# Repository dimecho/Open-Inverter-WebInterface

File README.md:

# Open Inverter - Alternative Web Interface

Alternative Web Interface for [OpenInverter.org Project](https://openinverter.org/forum)

- Inverter [Hardware](https://github.com/jsphuebner/inverter-hardware)
- Inverter [Firmware](https://github.com/jsphuebner/stm32-sine)
- Original [Web Interface](https://github.com/jsphuebner/esp8266-web-interface)

## Features

> **All-in-One**
> * RS232-USB Drivers
> * Inverter Parameters
> * Sensor Graphs
> * Firmware Flash
> * Wiring Diagrams
> * PCB Schematics
> * Component List
> * Encoder Builder
> * IGBT Test
> * CAN Setup
> * Auto Tunning
> * Source Code Compilers

## Screenshot

## Download

 [Download for Mac](../../releases/download/1.0/Open.Inverter.Web.dmg)

 [Download for Windows](../../releases/download/1.0/Open.Inverter.Web.zip)

 [Download for Linux](../../releases/download/1.0/Open.Inverter.Web.tgz)

 [Download for ESP8266](../../releases/download/1.0/Open.Inverter.ESP8266.zip)

 [Download for RaspberryPi](../../releases/download/1.0/Open.Inverter.Pi.zip)

## Author

Dima Dykhman

## Licenses

> Console Management
>
> 
>
> Inverter Hardware
>
> 
>
> Inverter Software
>
>

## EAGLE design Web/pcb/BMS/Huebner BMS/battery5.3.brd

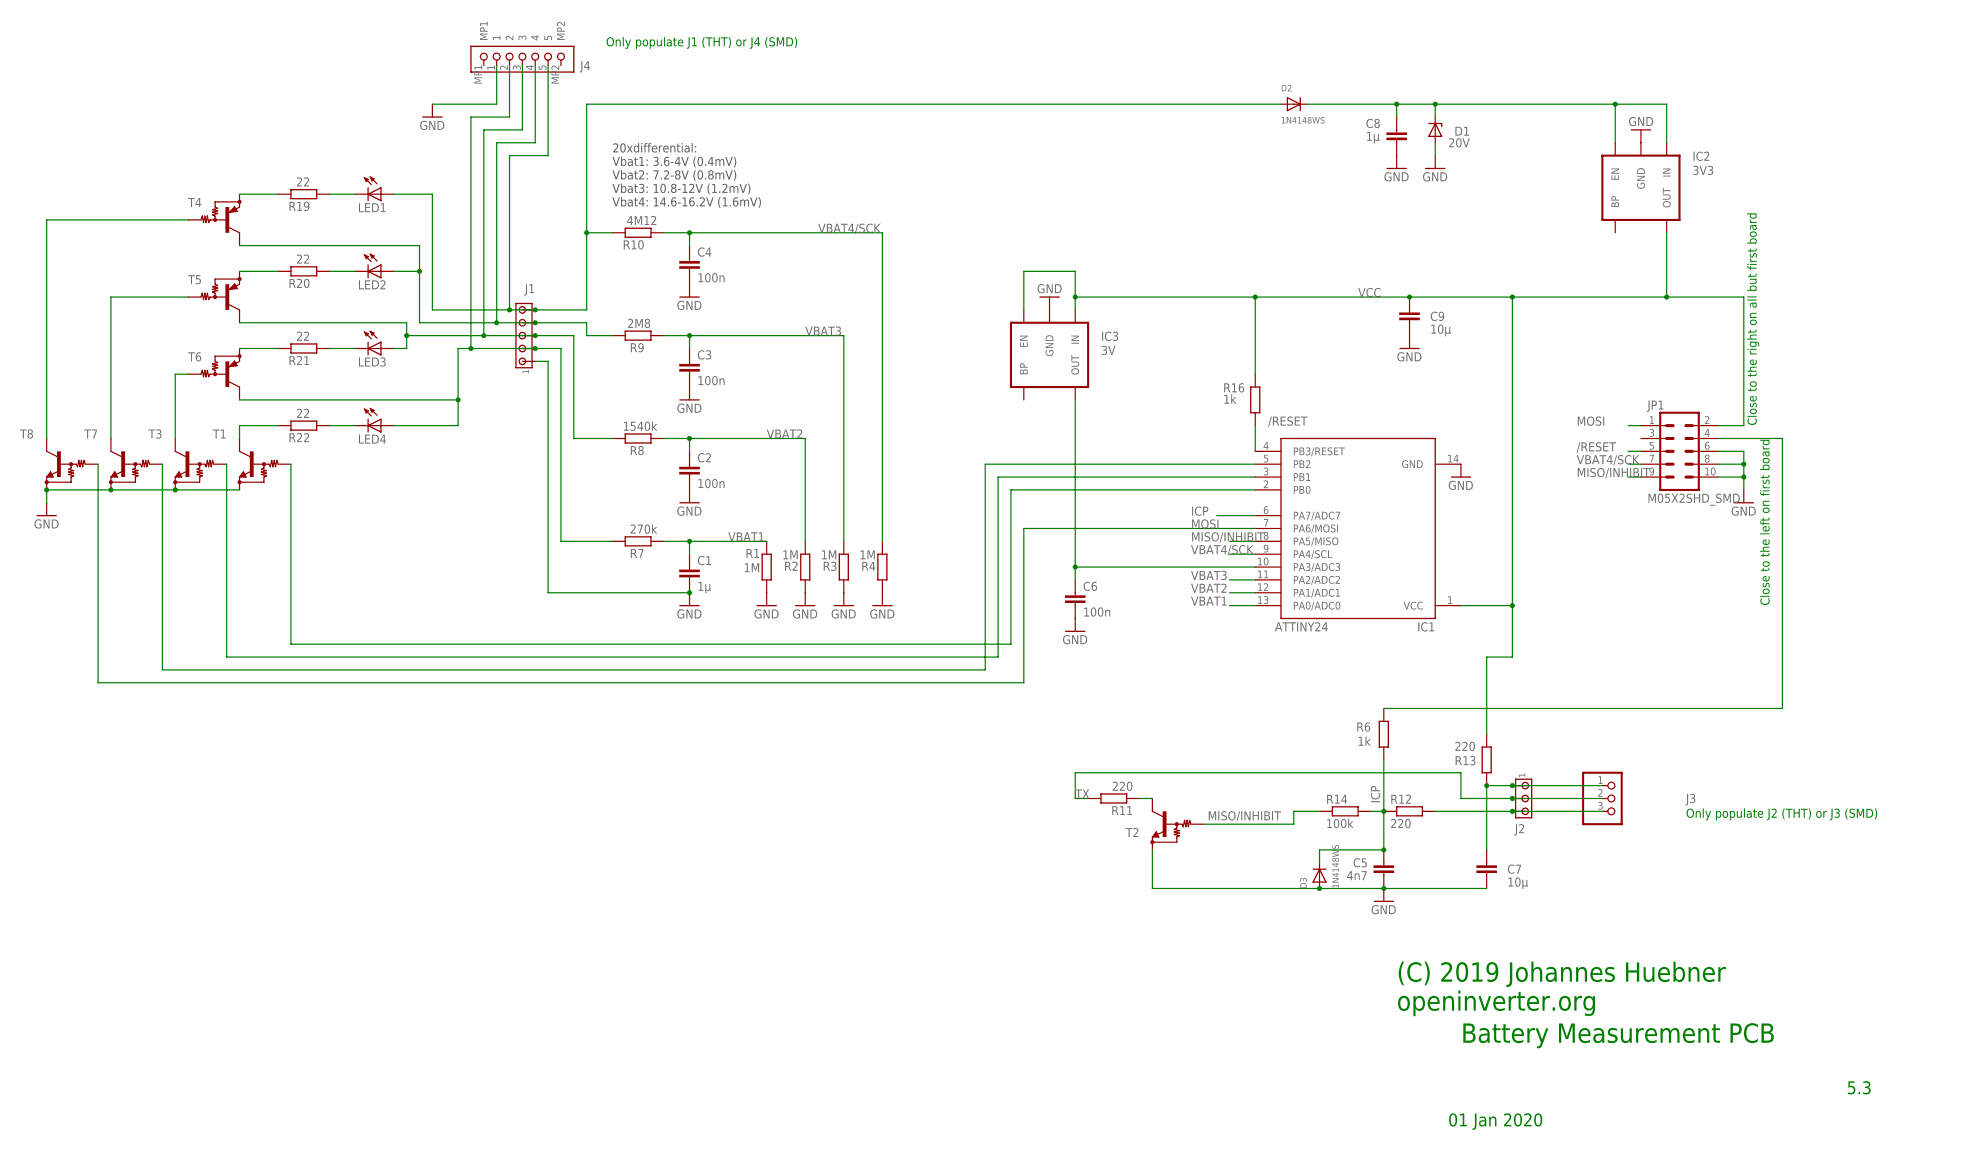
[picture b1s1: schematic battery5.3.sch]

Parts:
C1: 1µ; C0603
C2, C3, C4, C6: 100n; C0603
C5: 4n7; C0603
C7, C9: 10µ; C0805
C8: 1µ; C0805
D1: 20V; SMB
D2, D3: 1N4148WS; SOD-323F
IC1: ATTINY24; SO014
IC2: 3V3; SOT23-5
IC3: 3V; SOT23-5
J1: MTA05-100; 10X05MTA
J2: MTA03-100; 10X03MTA
J3: JST_3PIN; JSTPH3
J4: BM05B-PASS-1-TFT_(LF)(SN)SMD; BM05BPASS1TFTLFSN
JP1: M05X2SHD_SMD; 2X5-SHROUDED_SMD
LED1, LED2, LED3, LED4: 150060GS75000; CHIPLED_0805
R1, R2, R3, R4: 1M; R0603
R6, R16: 1k; R0603
R7: 270k; R0603
R8: 1540k; R0603
R9: 2M8; R0603
R10: 4M12; R0603
R11, R12, R13: 220; R0603
R14: 100k; R0603
R19, R20, R21, R22: 22; R0805
T1, T2, T3, T7, T8: MMUN2233; SC59-BEC
T4, T5, T6: MMUN2111LT1G; SC59-BEC

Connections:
/RESET: IC1.4 (PB3/RESET), JP1.5, R16.2
GND: C1.2, C2.2, C3.2, C4.2, C5.2, C6.2, C7.2, C8.2, C9.2, D1.A, D3.A, IC1.14 (GND), IC2.2 (GND), IC3.2 (GND), J1.1, J4.1, JP1.6, JP1.8, JP1.10, R1.2, R2.2, R3.2, R4.2, T1.E, T2.E, T3.E, T7.E, T8.E
ICP: C5.1, D3.C, IC1.6 (PA7/ADC7), R6.1, R12.1, R14.2
MISO/INHIBIT: IC1.8 (PA5/MISO), JP1.9, R14.1, T2.B
MOSI: IC1.7 (PA6/MOSI), JP1.1, T8.B
unnamed: T3.C, T6.B
unnamed: C6.1, IC1.10 (PA3/ADC3), IC3.5 (OUT)
unnamed: IC1.2 (PB0), T1.B
unnamed: IC1.3 (PB1), T3.B
unnamed: R19.2, T4.E
unnamed: LED1.C, R19.1
unnamed: JP1.4, R6.2
unnamed: IC1.5 (PB2), T7.B
unnamed: R20.2, T5.E
unnamed: C7.1, J2.1, J3.1, R13.2
unnamed: LED2.C, R20.1
unnamed: R11.1, T2.C
unnamed: D2.A, J1.5, J4.5, LED1.A, R10.2
unnamed: LED3.C, R21.1
unnamed: LED4.C, R22.1
unnamed: R21.2, T6.E
unnamed: R22.2, T1.C
unnamed: J2.3, J3.3, R12.2
unnamed: J1.4, J4.4, LED2.A, R9.2, T4.C
unnamed: J1.3, J4.3, LED3.A, R8.2, T5.C
unnamed: J1.2, J4.2, LED4.A, R7.2, T6.C
unnamed: T5.B, T7.C
unnamed: T4.B, T8.C
TX: J2.2, J3.2, R11.2
VBAT: C8.1, D1.C, D2.C, IC2.1 (IN), IC2.3 (EN)
VBAT1: C1.1, IC1.13 (PA0/ADC0), R1.1, R7.1
VBAT2: C2.1, IC1.12 (PA1/ADC1), R2.1, R8.1
VBAT3: C3.1, IC1.11 (PA2/ADC2), R3.1, R9.1
VBAT4/SCK: C4.1, IC1.9 (PA4/SCL), JP1.7, R4.1, R10.1
VCC: C9.1, IC1.1 (VCC), IC2.5 (OUT), IC3.1 (IN), IC3.3 (EN), JP1.2, R13.1, R16.1

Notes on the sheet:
20xdifferential: Vbat1: 3.6-4V (0.4mV) Vbat2: 7.2-8V (0.8mV) Vbat3: 10.8-12V (1.2mV) Vbat4: 14.6-16.2V (1.6mV)
Close to the right on all but first board
5.3
(C) 2019 Johannes Huebner openinverter.org
Battery Measurement PCB
01 Jan 2020
Only populate J2 (THT) or J3 (SMD)
Only populate J1 (THT) or J4 (SMD)
Close to the left on first board

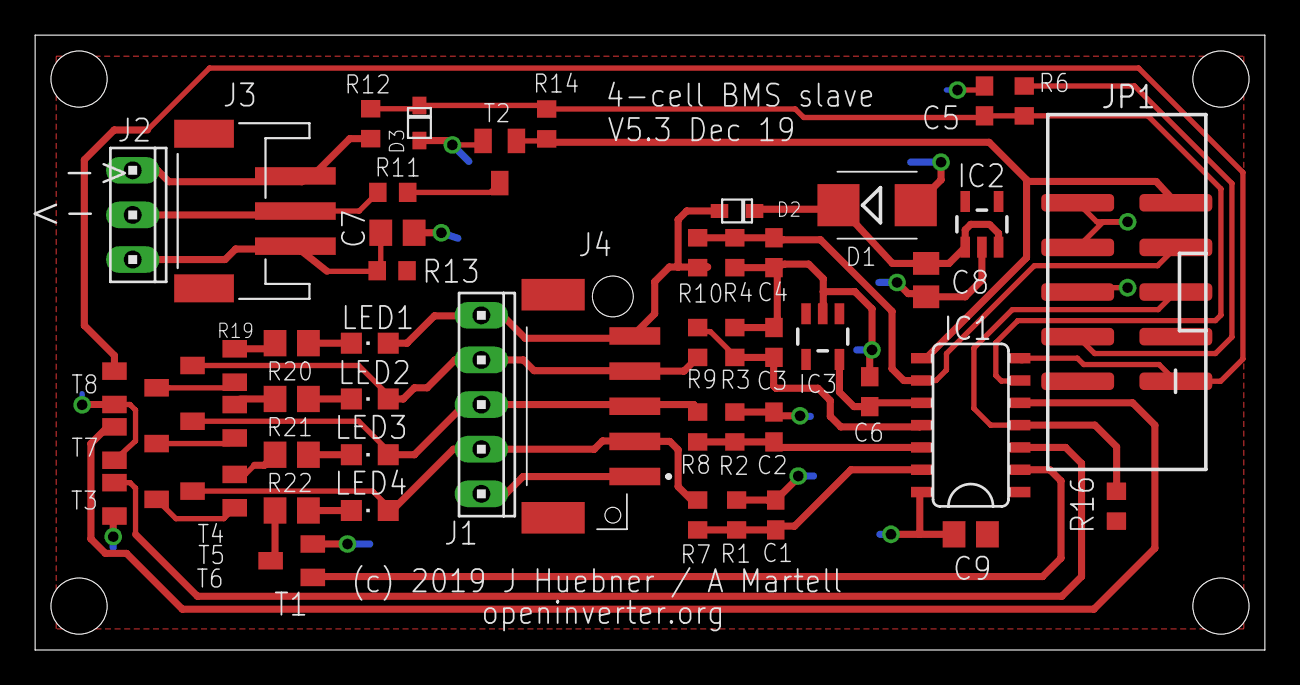
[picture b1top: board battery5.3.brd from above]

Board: 2 copper layers, 70.0 x 35.0 mm, 50 parts (0 on the bottom side), 35 nets.

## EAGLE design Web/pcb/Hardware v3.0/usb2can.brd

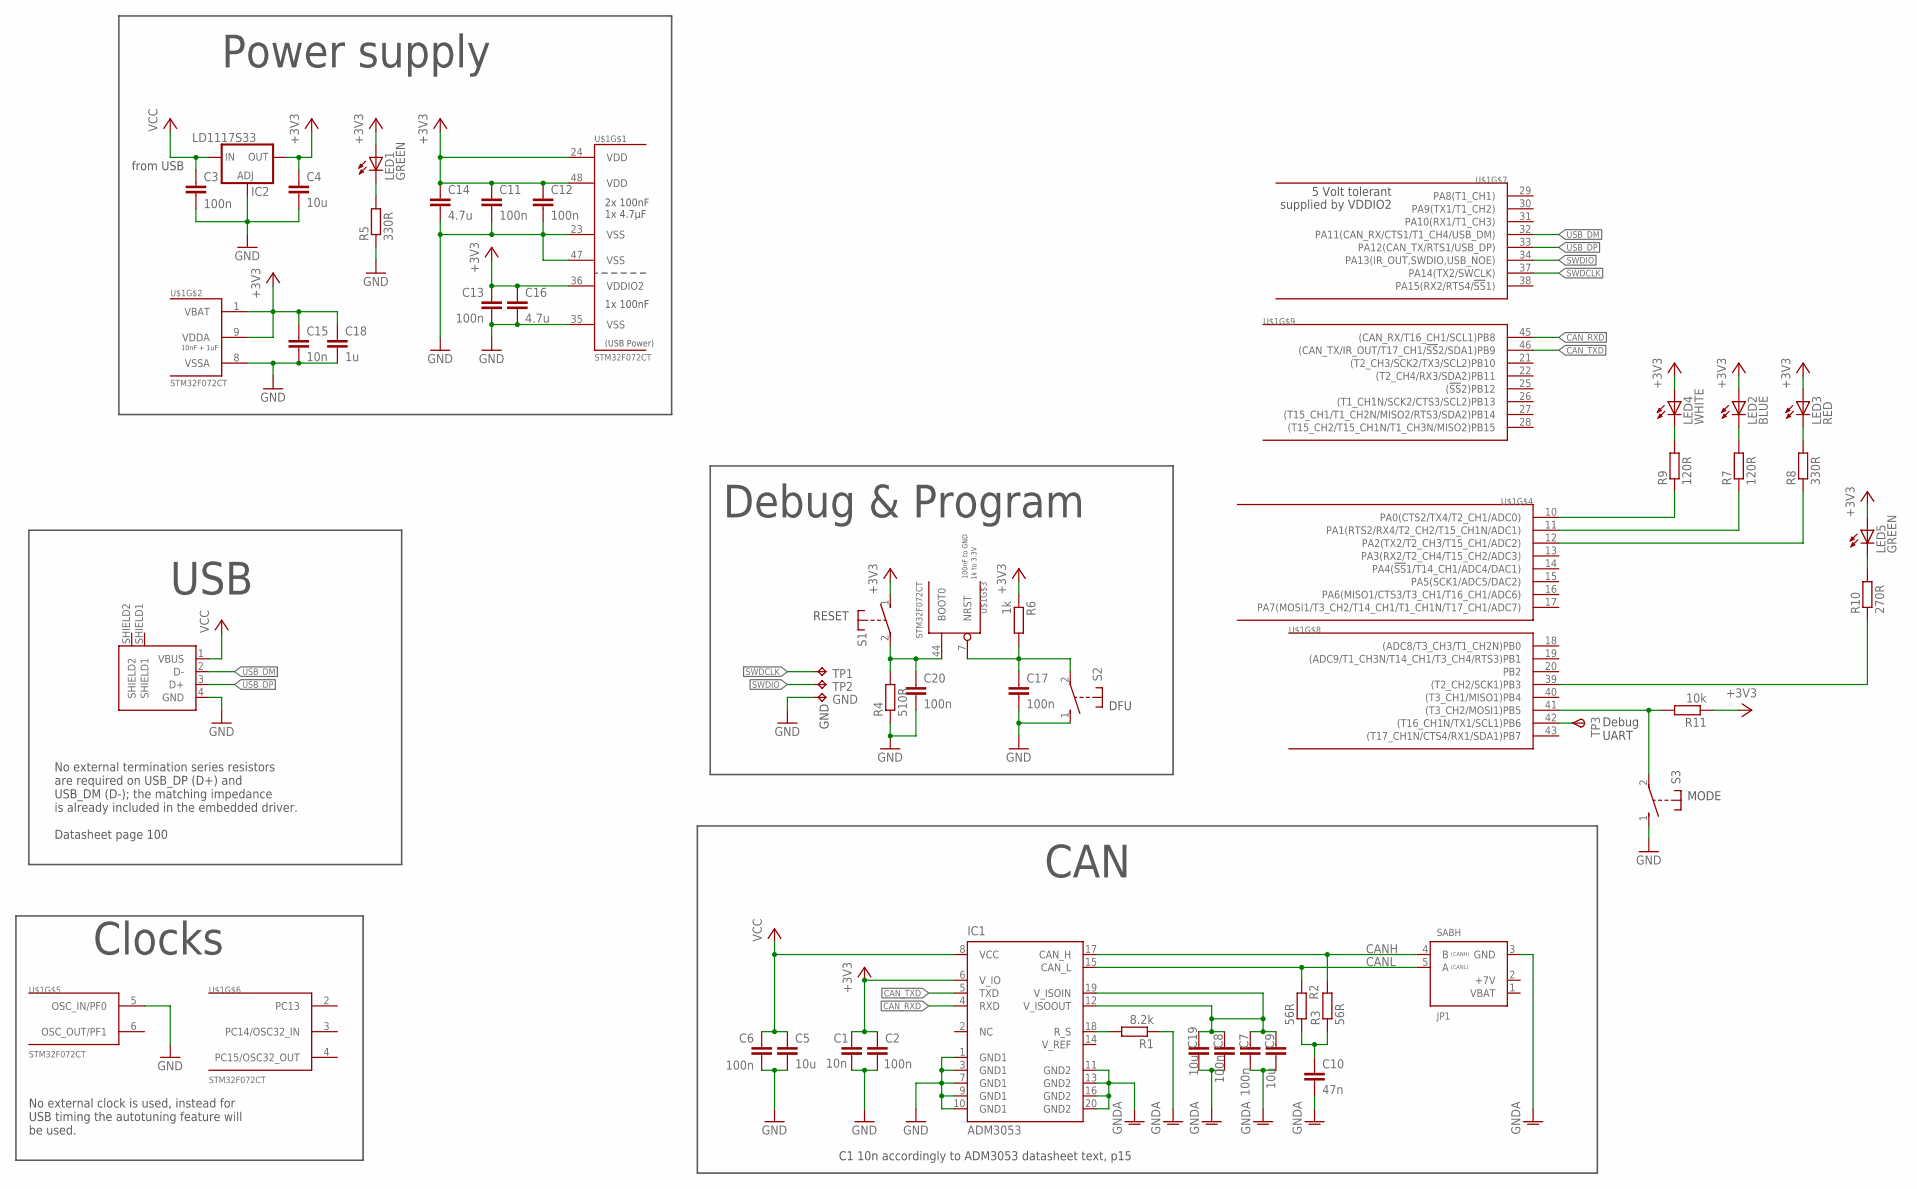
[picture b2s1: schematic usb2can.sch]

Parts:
C1: 10n; C0603K
C2, C3, C6: 100n; C0603K
C4, C5, C9, C19: 10u; C0805K
C7, C8: 100n; C0805K
C10: 47n; C0603K
C11, C12, C13, C17, C20: 100n; C0603
C14, C16: 4.7u; C0805K
C15: 10n; C0603
C18: 1u; C0805K
CON1: USB_A_MALESMD; USB_A_MALE_SMD
GND: TPB2,54; B2,54
IC1: ADM3053; SO20L
IC2: LD1117S33; SOT223
JP1: SABH; 7395-05
LED1, LED5: GREEN; CHIPLED_0603
LED2: BLUE; CHIPLED_0603
LED3: RED; CHIPLED_0603
LED4: WHITE; CHIPLED_0603
R1: 8.2k; R0603
R2, R3: 56R; R0805
R4: 510R; R0603
R5, R8: 330R; R0603
R6: 1k; R0603
R7, R9: 120R; R0603
R10: 270R; R0603
R11: 10k; R0603
S1, S2, S3: MICRO_SWITCH_3X6X2.5S; MICRO_SWITCH_3X6X2.5
TP1, TP2: TPB2,54; B2,54
TP3: TPSTP07R; TP07R
U$1: STM32F072CT; TQFP48

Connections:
+3V3: C1.1, C2.1, C4.1, C11.1, C12.1, C13.1, C14.1, C15.1, C16.1, C18.1, IC1.6 (V_IO), IC2.4 (OUT), LED1.A, LED2.A, LED3.A, LED4.A, LED5.A, R6.1, R11.1, S1.1, U$1.1 (VBAT), U$1.9 (VDDA), U$1.24 (VDD), U$1.36 (VDDIO2), U$1.48 (VDD)
CANH: IC1.17 (CAN_H), JP1.4 (B), R3.2
CANL: IC1.15 (CAN_L), JP1.5 (A), R2.2
CAN_RXD: IC1.4 (RXD), U$1.45 ((CAN_RX/T16_CH1/SCL1)PB8)
CAN_TXD: IC1.5 (TXD), U$1.46 ((CAN_TX/IR_OUT/T17_CH1/!SS!2/SDA1)PB9)
GND: C1.2, C2.2, C3.2, C4.2, C5.2, C6.2, C11.2, C12.2, C13.2, C14.2, C15.2, C16.2, C17.2, C18.2, C20.2, CON1.4 (GND), GND.TP, IC1.1 (GND1), IC1.3 (GND1), IC1.7 (GND1), IC1.9 (GND1), IC1.10 (GND1), IC2.1 (ADJ), R4.1, R5.1, S2.1, S3.1, U$1.5 (OSC_IN/PF0), U$1.8 (VSSA), U$1.23 (VSS), U$1.35 (VSS), U$1.47 (VSS)
GNDA: C7.2, C8.2, C9.2, C10.2, C19.2, IC1.11 (GND2), IC1.13 (GND2), IC1.16 (GND2), IC1.20 (GND2), JP1.3 (GND), R1.1
unnamed: IC1.18 (R_S), R1.2
unnamed: C10.1, R2.1, R3.1
unnamed: LED1.C, R5.2
unnamed: C20.1, R4.2, S1.2, U$1.44 (BOOT0)
unnamed: C17.1, R6.2, S2.2, U$1.7 (NRST)
unnamed: C7.1, C8.1, C9.1, C19.1, IC1.12 (V_ISOOUT), IC1.19 (V_ISOIN)
unnamed: LED2.C, R7.2
unnamed: R11.2, S3.2, U$1.41 ((T3_CH2/MOSI1)PB5)
unnamed: LED3.C, R8.2
unnamed: LED4.C, R9.2
unnamed: R9.1, U$1.10 (PA0(CTS2/TX4/T2_CH1/ADC0))
unnamed: R7.1, U$1.11 (PA1(RTS2/RX4/T2_CH2/T15_CH1N/ADC1))
unnamed: R8.1, U$1.12 (PA2(TX2/T2_CH3/T15_CH1/ADC2))
unnamed: LED5.C, R10.2
unnamed: R10.1, U$1.39 ((T2_CH2/SCK1)PB3)
SWDCLK: TP1.TP, U$1.37 (PA14(TX2/SWCLK))
SWDIO: TP2.TP, U$1.34 (PA13(IR_OUT,SWDIO,USB_NOE))
TX: TP3.TP, U$1.42 ((T16_CH1N/TX1/SCL1)PB6)
USB_DM: CON1.2 (D-), U$1.32 (PA11(CAN_RX/CTS1/T1_CH4/USB_DM))
USB_DP: CON1.3 (D+), U$1.33 (PA12(CAN_TX/RTS1/USB_DP))
VCC: C3.1, C5.1, C6.1, CON1.1 (VBUS), IC1.8 (VCC), IC2.3 (IN)

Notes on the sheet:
CAN
No external termination series resistors are required on USB_DP (D+) and USB_DM (D-); the matching impedance is already included in the embedded driver. Datasheet page 100
USB
Clocks
No external clock is used, instead for USB timing the autotuning feature will be used.
from USB
Power supply
Debug & Program
Debug UART
C1 10n accordingly to ADM3053 datasheet text, p15
DFU
RESET
MODE

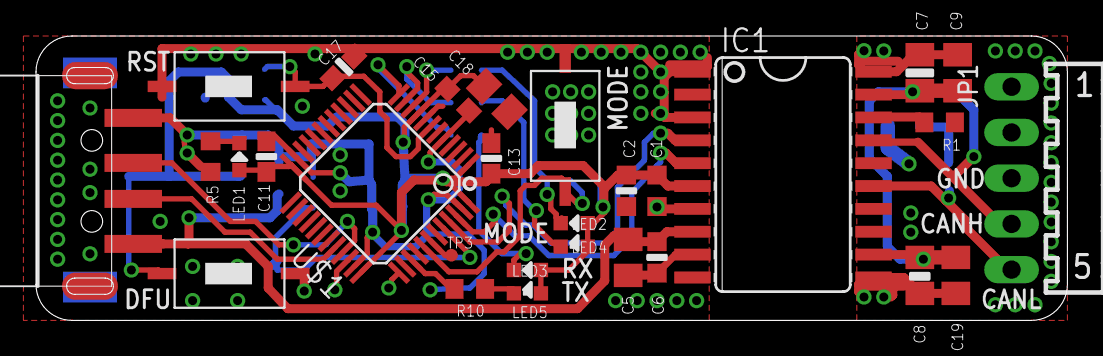
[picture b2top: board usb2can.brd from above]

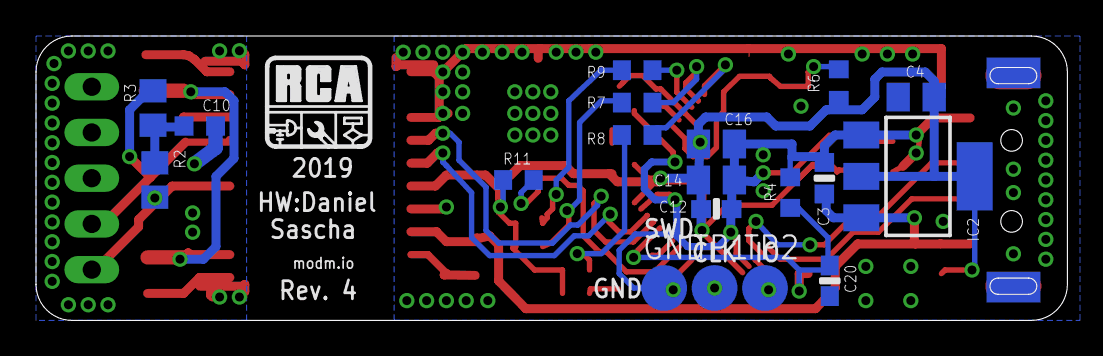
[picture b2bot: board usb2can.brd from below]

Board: 2 copper layers, 57.3 x 15.8 mm, 49 parts (19 on the bottom side), 28 nets.

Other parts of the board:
U$2: LOGO_SILK_BOT

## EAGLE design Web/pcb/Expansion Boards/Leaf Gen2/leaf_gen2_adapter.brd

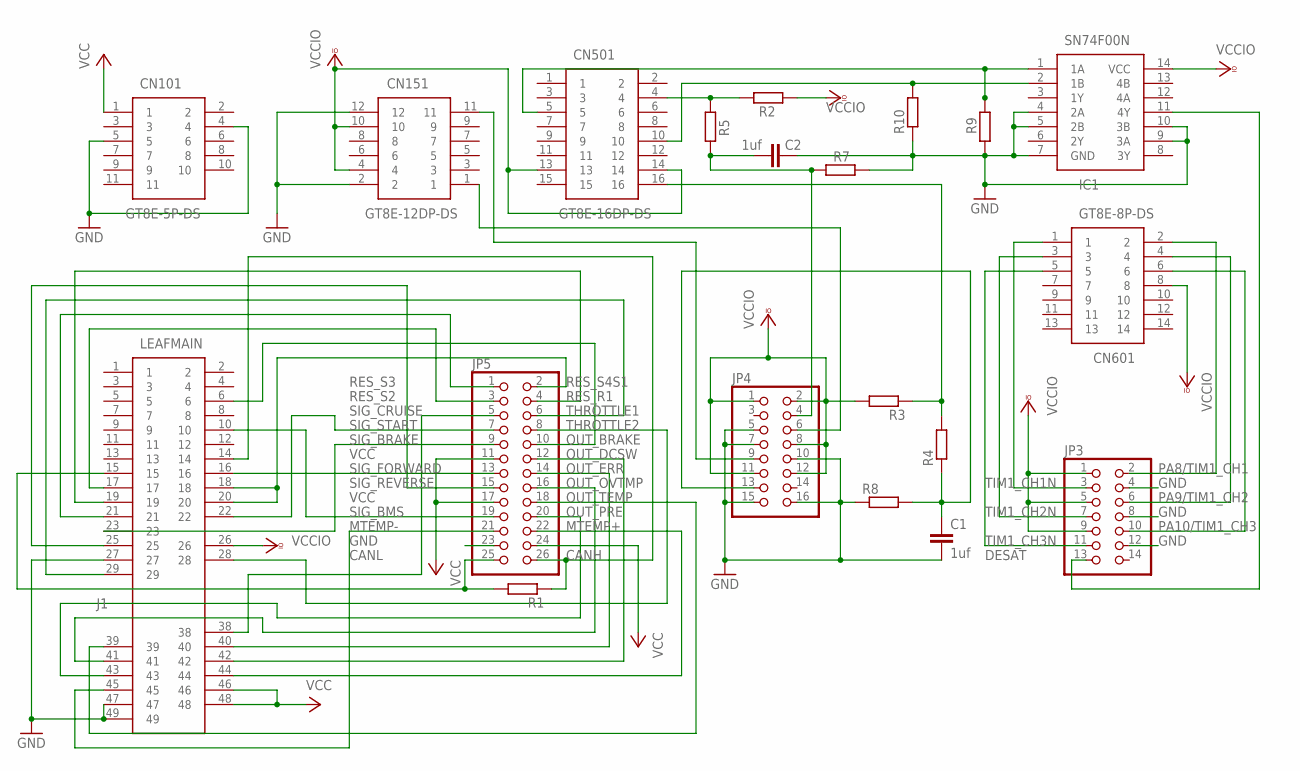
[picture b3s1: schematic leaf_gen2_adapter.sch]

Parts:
C1, C2: 1uf; C025-024X044
CN101: GT8E-5P-DS; GT8E5PDS
CN151: GT8E-12DP-DS
CN501: GT8E-16DP-DS
CN601: GT8E-8P-DS; GT8E8PDS
IC1: SN74F00N; DIP254P762X508-14
J1: LEAFMAIN
JP3: PINHD-2X7; 2X07
JP4: PINHD-2X8; 2X08
JP5: PINHD-2X13; 2X13
R1, R2, R3, R4, R5, R7, R8, R9, R10: R-EU_0207/12; 0207/12

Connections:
CANH: J1.14, JP5.26, R1.1
CANL: J1.15, JP5.25, R1.2
DESAT: IC1.11 (4Y), JP3.13
GND: C1.2, C2.1, CN101.4, CN101.5, CN151.2, CN151.12, IC1.4 (2A), IC1.5 (2B), IC1.7 (GND), IC1.9 (3A), IC1.10 (3B), J1.27, J1.47, J1.49, JP3.4, JP3.8, JP3.12, JP4.5, JP4.7, JP4.10, JP4.15, JP4.16, JP5.23, R7.2, R8.1, R9.1, R10.1
MTEMP+: J1.44, JP5.22
MTEMP-: J1.45, JP5.21
unnamed: C1.1, JP4.13, R4.1, R8.2
unnamed: CN501.16, R3.1, R4.2
unnamed: CN151.1, JP4.6
unnamed: CN501.4, R2.2, R5.1
unnamed: C2.2, JP4.4, R5.2, R7.1
unnamed: CN501.5, IC1.1 (1A), R9.2
unnamed: CN501.10, IC1.2 (1B), R10.2
unnamed: CN151.11, JP4.9
OUT_BRAKE: J1.6, JP5.10
OUT_DCSW: J1.42, JP5.12
OUT_ERR: J1.40, JP5.14
OUT_OVTMP: J1.41, JP5.16
OUT_PRE: J1.43, JP5.20
OUT_TEMP: J1.39, JP5.18
PA8/TIM1_CH1: CN601.2, JP3.2
PA9/TIM1_CH2: CN601.4, JP3.6
PA10/TIM1_CH3: CN601.6, JP3.10
RES_R1: J1.19, JP5.4
RES_S2: J1.17, JP5.3
RES_S3: J1.21, JP5.1
RES_S4S1: J1.18, J1.20, JP5.2
SIG_BMS: J1.10, JP5.19
SIG_BRAKE: J1.23, JP5.9
SIG_CRUISE: J1.38, JP5.5
SIG_FORWARD: J1.16, JP5.13
SIG_REVERSE: J1.25, JP5.15
SIG_START: J1.22, JP5.7
THROTTLE1: J1.29, JP5.6
THROTTLE2: J1.28, JP5.8
TIM1_CH1N: CN601.1, JP3.3
TIM1_CH2N: CN601.3, JP3.7
TIM1_CH3N: CN601.5, JP3.11
VCC: CN101.1, J1.46, J1.48, JP5.11, JP5.17, JP5.24
VCCIO: CN151.4, CN151.10, CN501.13, CN501.14, CN601.8, IC1.14 (VCC), J1.26, JP3.1, JP3.5, JP3.9, JP4.1, JP4.2, JP4.8, JP4.11, JP4.12, R2.1, R3.2

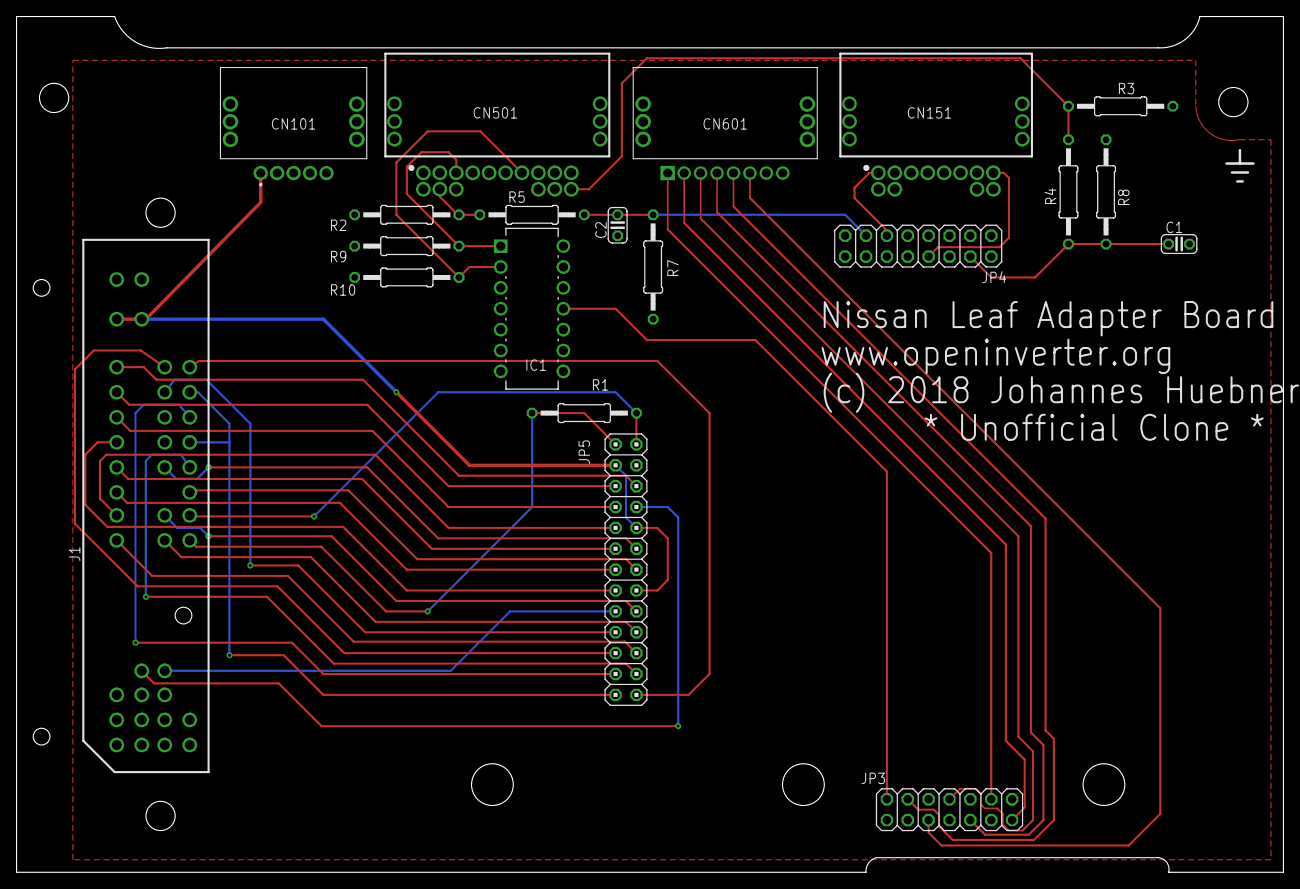
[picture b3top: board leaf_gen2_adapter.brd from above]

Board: 2 copper layers, 154.2 x 104.1 mm, 20 parts (0 on the bottom side), 40 nets.

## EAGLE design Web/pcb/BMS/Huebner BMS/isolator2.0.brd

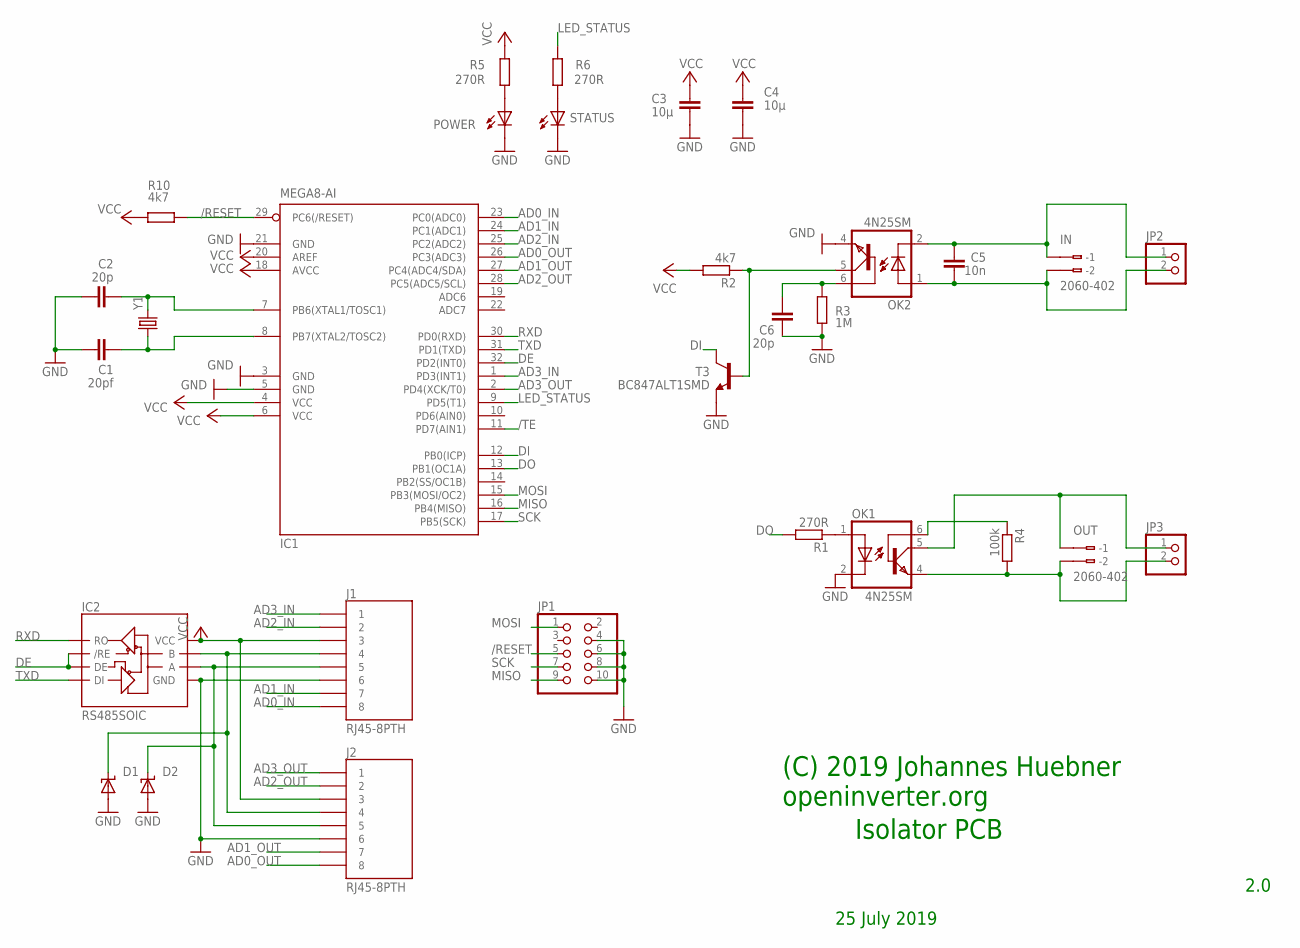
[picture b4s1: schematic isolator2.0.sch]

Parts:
C1: 20pf; C0805
C2, C6: 20p; C0805
C3, C4: 10µ; C0805
C5: 10n; C0805
D1, D2: SUPPRESSOR-SMBJ; SMBJ
IC1: MEGA8-AI; TQFP32-08
IC2: RS485SOIC; SO08
IN: 2060-402
J1, J2: RJ45-8PTH; RJ45-8
JP1: PINHD-2X5; 2X05
JP2, JP3: PINHD-1X2; 1X02
OK1, OK2: 4N25SM; DIL6-SMD
OUT: 2060-402
POWER: LEDCHIP-LED0805; CHIP-LED0805
R1, R5, R6: 270R; M0805
R2, R10: 4k7; M0805
R3: 1M; M0805
R4: 100k; M0805
STATUS: LEDCHIP-LED0805; CHIP-LED0805
T3: BC847ALT1SMD; SOT23
Y1: CRYSTAL10.5X4.8; CRYSTAL-SMD-10.5X4.8-2PIN

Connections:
/RESET: IC1.29 (PC6(/RESET)), JP1.5, R10.2
/TE: IC1.11 (PD7(AIN1))
AD0_IN: IC1.23 (PC0(ADC0)), J1.8
AD0_OUT: IC1.26 (PC3(ADC3)), J2.8
AD1_IN: IC1.24 (PC1(ADC1)), J1.7
AD1_OUT: IC1.27 (PC4(ADC4/SDA)), J2.7
AD2_IN: IC1.25 (PC2(ADC2)), J1.2
AD2_OUT: IC1.28 (PC5(ADC5/SCL)), J2.2
AD3_IN: IC1.1 (PD3(INT1)), J1.1
AD3_OUT: IC1.2 (PD4(XCK/T0)), J2.1
DE: IC1.32 (PD2(INT0)), IC2.2 (/RE), IC2.3 (DE)
DI: IC1.12 (PB0(ICP)), T3.3 (C)
DO: IC1.13 (PB1(OC1A)), R1.2
GND: C1.1, C2.1, C3.2, C4.2, C6.1, D1.A, D2.A, IC1.3 (GND), IC1.5 (GND), IC1.21 (GND), IC2.5 (GND), J1.6, J2.6, JP1.4, JP1.6, JP1.8, JP1.10, OK1.2 (C), OK2.4 (EMI), POWER.C, R3.2, STATUS.C, T3.2 (E)
LED_STATUS: IC1.9 (PD5(T1)), R6.2
MISO: IC1.16 (PB4(MISO)), JP1.9
MOSI: IC1.15 (PB3(MOSI/OC2)), JP1.1
unnamed: OK1.1 (A), R1.1
unnamed: C6.2, OK2.6 (BAS), R3.1
unnamed: OK2.5 (COL), R2.1, T3.1 (B)
unnamed: OK1.6 (BAS), R4.1
unnamed: D1.C, IC2.7 (B), J1.4, J2.4
unnamed: JP3.2, OK1.4 (EMI), OUT.P22 (B-2), R4.2
unnamed: D2.C, IC2.6 (A), J1.5, J2.5
unnamed: POWER.A, R5.1
unnamed: R6.1, STATUS.A
unnamed: C2.2, IC1.7 (PB6(XTAL1/TOSC1)), Y1.P$2 (2)
unnamed: C1.2, IC1.8 (PB7(XTAL2/TOSC2)), Y1.P$1 (1)
unnamed: C5.1, IN.P22 (B-2), JP2.2, OK2.1 (A)
unnamed: C5.2, IN.P21 (B-1), JP2.1, OK2.2 (C)
unnamed: JP3.1, OK1.5 (COL), OUT.P21 (B-1)
RXD: IC1.30 (PD0(RXD)), IC2.1 (RO)
SCK: IC1.17 (PB5(SCK)), JP1.7
TXD: IC1.31 (PD1(TXD)), IC2.4 (DI)
VCC: C3.1, C4.1, IC1.4 (VCC), IC1.6 (VCC), IC1.18 (AVCC), IC1.20 (AREF), IC2.8 (VCC), J1.3, J2.3, R2.2, R5.2, R10.1

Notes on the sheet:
(C) 2019 Johannes Huebner openinverter.org
Isolator PCB
2.0
25 July 2019

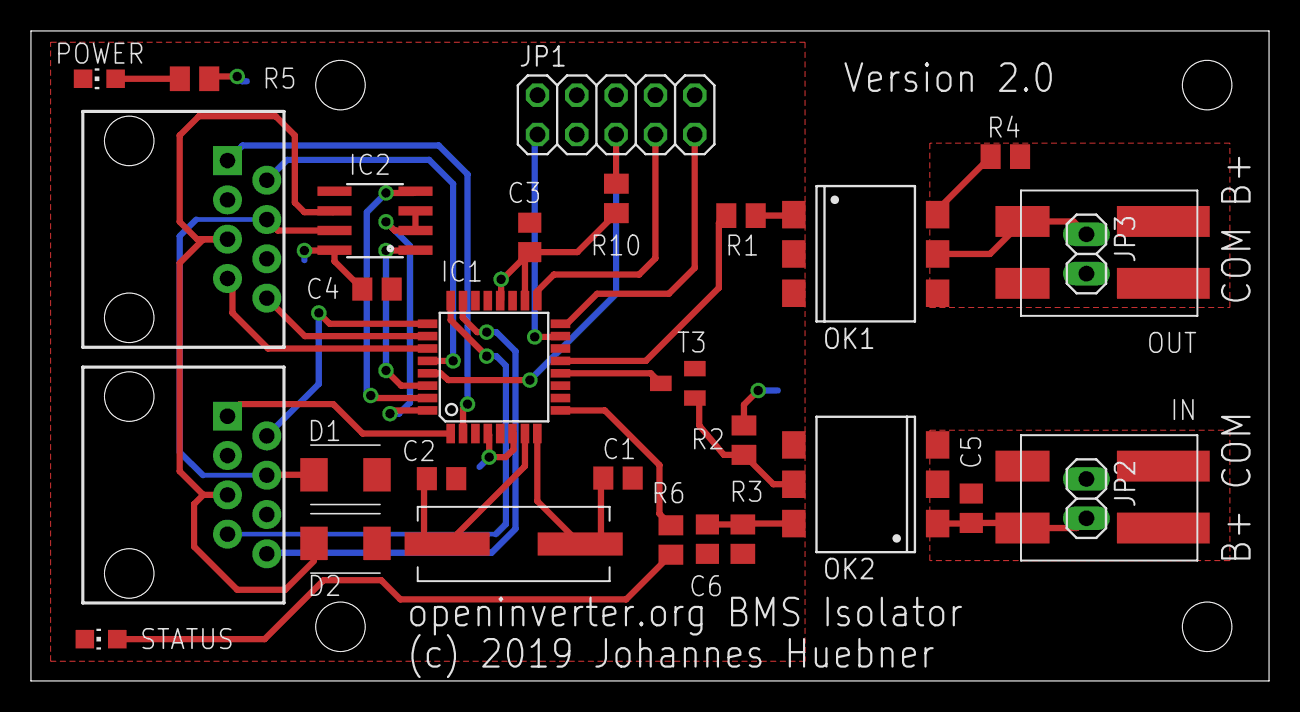
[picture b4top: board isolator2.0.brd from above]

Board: 2 copper layers, 80.0 x 42.0 mm, 30 parts (0 on the bottom side), 34 nets.

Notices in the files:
README.md:
Licenses:
> [CC0](https://creativecommons.org/publicdomain/zero/1.0/)
> Inverter Hardware
> [CC BY-SA 4.0](https://creativecommons.org/licenses/by-sa/4.0/legalcode)
> Inverter Software
> [BSD](https://www.gnu.org/licenses/)
CC0
Web/pcb/BMS/Huebner BMS/battery5.3.brd:
(c) 2019 J Huebner / A Martell
Web/pcb/Expansion Boards/Leaf Gen2/leaf_gen2_adapter.brd:
(c) 2018 Johannes Huebner
Web/pcb/Hardware v2.0/sensor_voltage.brd:
(c) 2018 J. Huebner
parts and their libraries:
SparkFun-PowerIC: Licensing: CC v3.0 Share-Alike You are welcome to use this library for commercial purposes.
